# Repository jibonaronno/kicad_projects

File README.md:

# kicad_projects
1. Trailing Edge Dimmer ESP8266

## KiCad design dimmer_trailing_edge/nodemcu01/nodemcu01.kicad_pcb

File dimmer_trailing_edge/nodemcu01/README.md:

# Trailing Edge Dimmer Description

Practically there are 2 types of dimmer. 

1. Raising Edge
2. Trailing Edge

Based on the swithing time position after zero cross detection. 

Here is a simple concept of raising and trailing edge switching.

This project focused on trailing edge dimmer construction. 

Here it stores energy in C5 and C6 from power line ACL and ACN. From the perspective it only uses positive cycle of the phase to store energy. Turning on the mosfet is occured by Opto U2, and turning off is happened by R14 (10k) . So this dimmer is not suitable for more than 200W. 

Found another solution as below:

This 3 channel dimmer is build on ESP8266 NodeMCU . Complete Kicad Drawing is available in [https://github.com/jibonaronno/kicad_projects/tree/main/dimmer_trailing_edge/nodemcu01](https://github.com/jibonaronno/kicad_projects/tree/main/dimmer_trailing_edge/nodemcu01)

The Arduino code is available under qnod01 folder. It is required to provide correct Wifi credentials the the Arduino code and also need to find the IP address of NodeMCU. After successfull connection between Wifi and NodeMCU, user can browse to the NodeMCU IP Address from phone browser and control dimming.

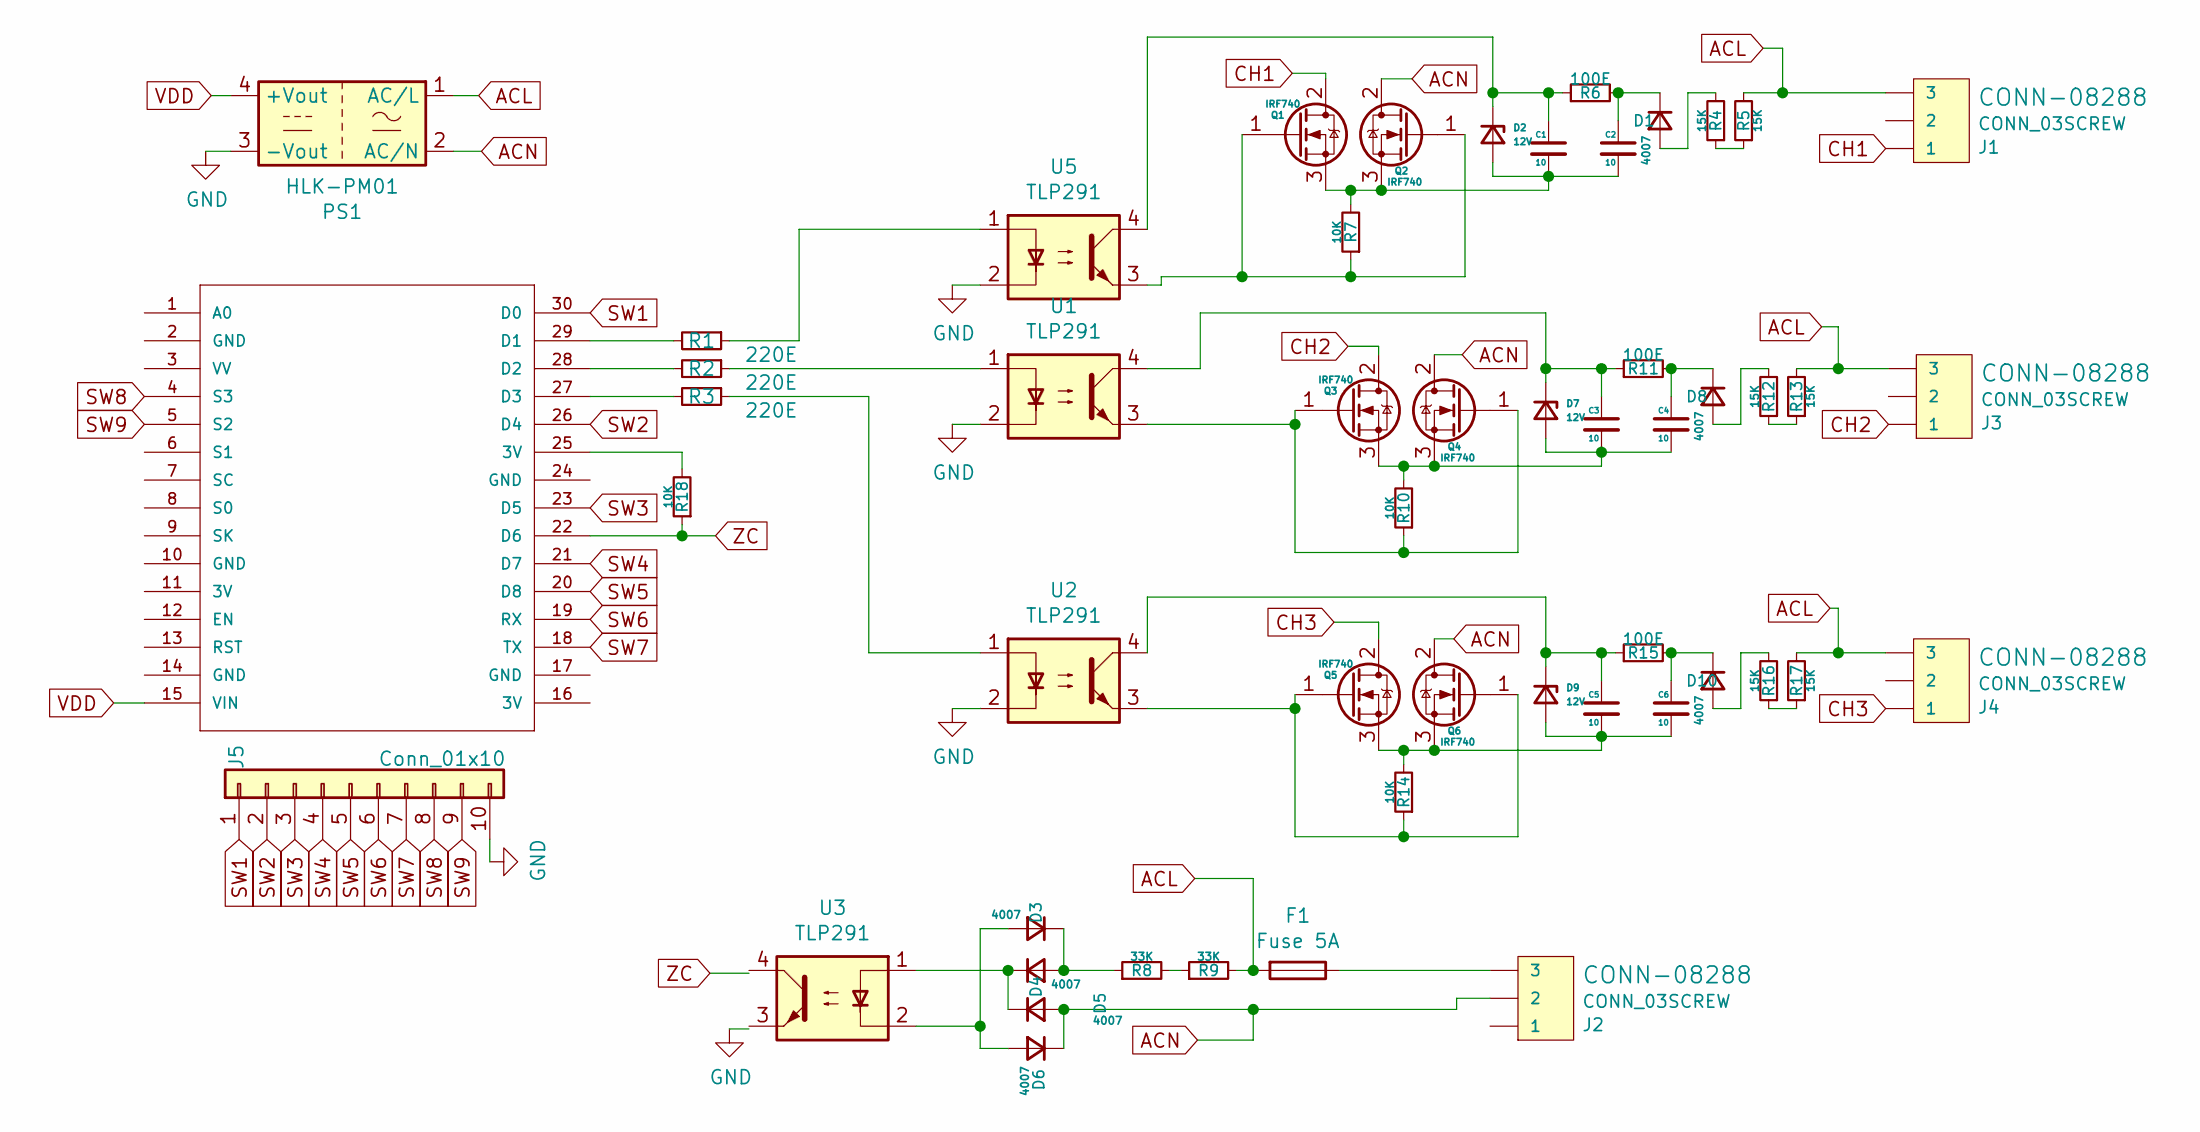
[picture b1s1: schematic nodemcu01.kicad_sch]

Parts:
C1, C2, C3, C4, C5, C6: 10; C_1206_3216Metric
D1, D3, D4, D5, D6, D8, D10: 4007; D_1206_3216Metric
D2, D7, D9: 12V; D_1206_3216Metric
F1: Fuse 5A; Fuseholder5x20_horiz_open_inline_Type-I
J1, J2, J3, J4: CONN_03SCREW; SCREWTERMINAL-3.5MM-3
J5: Conn_01x10; JST_XH_B10B-XH-A_1x10_P2.50mm_Vertical
M1: NODEMCU; nodemcu2-NODEMCU
PS1: HLK-PM01; Converter_ACDC_HiLink_HLK-PMxx
Q1, Q2, Q3, Q4, Q5, Q6: IRF740; TO-220-3_Vertical
R1, R2, R3: 220E; R_0805_2012Metric
R4, R5, R12, R13, R16, R17: 15K; R_1206_3216Metric
R6, R11, R15: 100E; R_1206_3216Metric
R7, R10, R14, R18: 10K; R_1206_3216Metric
R8, R9: 33K; R_1206_3216Metric
U1, U2, U3, U5: TLP291; SOIC-4_4.55x2.6mm_P1.27mm

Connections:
ACL: F1.2, J1.3, J3.3, J4.3, PS1.1 (AC/L), R5.2, R9.2, R13.2, R17.2
ACN: D5.2 (A), D6.1 (K), J2.2, PS1.2 (AC/N), Q2.2 (D), Q4.2 (D), Q6.2 (D)
CH1: J1.1, Q1.2 (D)
CH2: J3.1, Q3.2 (D)
CH3: J4.1, Q5.2 (D)
GND: J5.10, PS1.3 (-Vout), U1.2, U2.2, U3.3, U5.2
unnamed: C1.1, D2.1 (K), R6.1, U5.4
unnamed: C1.2, C2.2, D2.2 (A), Q1.3 (S), Q2.3 (S), R7.2
unnamed: C2.1, D1.1 (K), R6.2
unnamed: C3.1, D7.1 (K), R11.1, U1.4
unnamed: C3.2, C4.2, D7.2 (A), Q3.3 (S), Q4.3 (S), R10.2
unnamed: C4.1, D8.1 (K), R11.2
unnamed: C5.1, D9.1 (K), R15.1, U2.4
unnamed: C5.2, C6.2, D9.2 (A), Q5.3 (S), Q6.3 (S), R14.2
unnamed: C6.1, D10.1 (K), R15.2
unnamed: D1.2 (A), R4.2
unnamed: D3.1 (K), D4.2 (A), R8.1
unnamed: D3.2 (A), D6.2 (A), U3.2
unnamed: D4.1 (K), D5.1 (K), U3.1
unnamed: D8.2 (A), R12.2
unnamed: D10.2 (A), R16.2
unnamed: F1.1, J2.3
unnamed: M1.25 (3V), R18.2
unnamed: M1.27 (D3), R3.2
unnamed: M1.28 (D2), R2.2
unnamed: M1.29 (D1), R1.2
unnamed: Q1.1 (G), Q2.1 (G), R7.1, U5.3
unnamed: Q3.1 (G), Q4.1 (G), R10.1, U1.3
unnamed: Q5.1 (G), Q6.1 (G), R14.1, U2.3
unnamed: R1.1, U5.1
unnamed: R2.1, U1.1
unnamed: R3.1, U2.1
unnamed: R4.1, R5.1
unnamed: R8.2, R9.1
unnamed: R12.1, R13.1
unnamed: R16.1, R17.1
SW1: J5.1, M1.30 (D0)
SW2: J5.2, M1.26 (D4)
SW3: J5.3, M1.23 (D5)
SW4: J5.4, M1.21 (D7)
SW5: J5.5, M1.20 (D8)
SW6: J5.6, M1.19 (RX)
SW7: J5.7, M1.18 (TX)
SW8: J5.8, M1.4 (S3)
SW9: J5.9, M1.5 (S2)
VDD: M1.15 (VIN), PS1.4 (+Vout)
ZC: M1.22 (D6), R18.1, U3.4

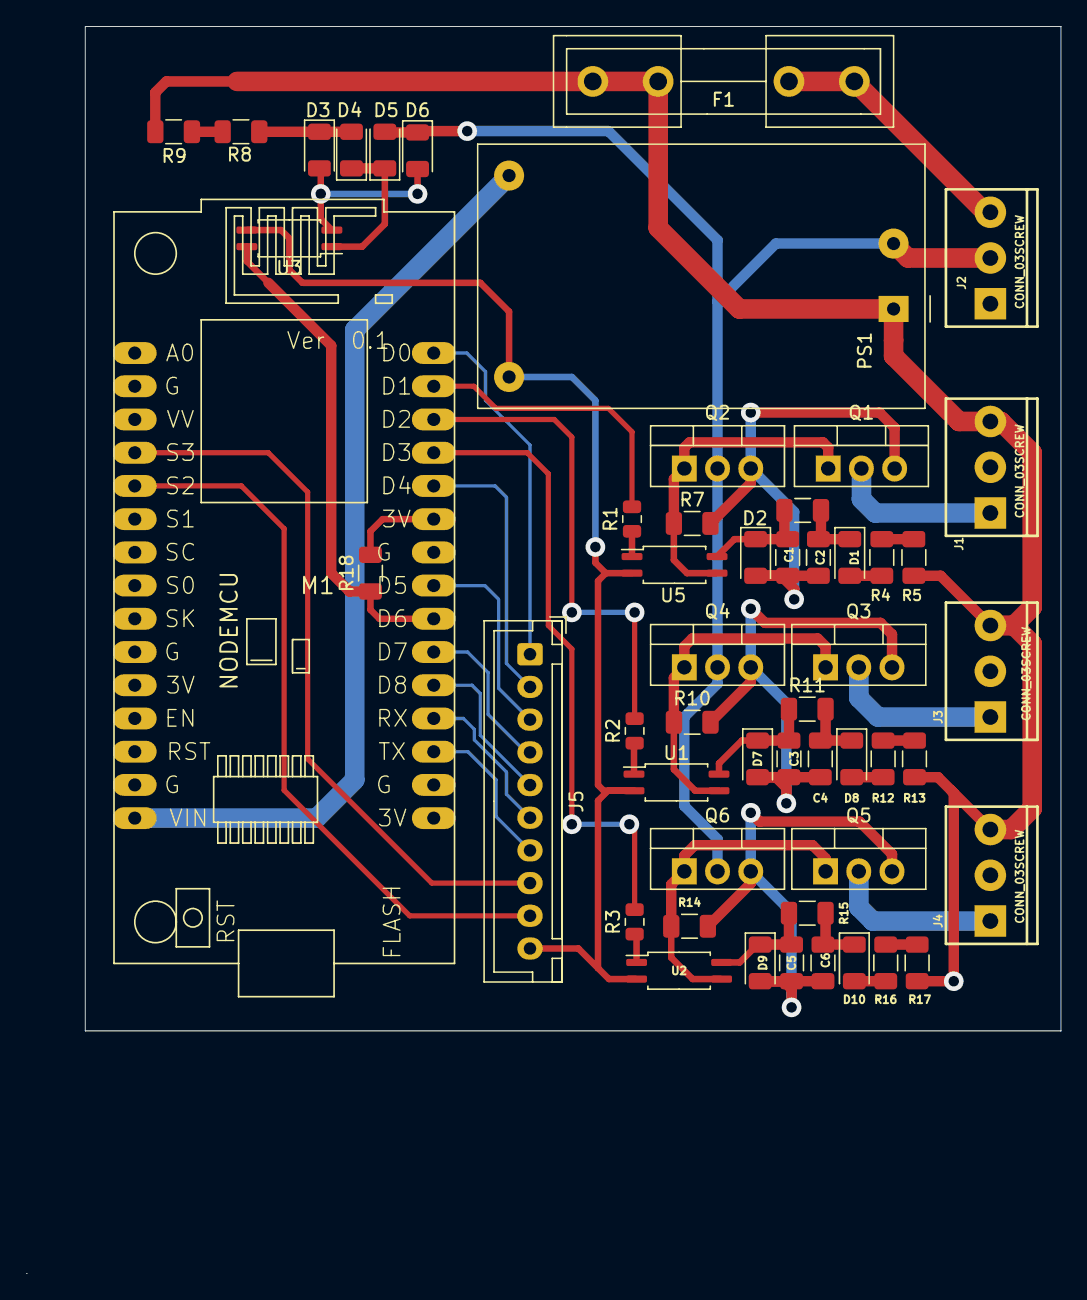
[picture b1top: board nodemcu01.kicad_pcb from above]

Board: 2 copper layers, 79.1 x 95.3 mm, 52 parts (0 on the bottom side), 47 nets.

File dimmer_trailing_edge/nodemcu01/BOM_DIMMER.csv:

"Item","Qty","Reference(s)","Value","LibPart","Footprint","Datasheet","Field4"
"1","6","C1, C2, C3, C4, C5, C6","10uF","Device:C_Small","Capacitor_SMD:C_1206_3216Metric","~",""
"2","7","D1, D3, D4, D5, D6, D8, D10","4007","Device:D_Small","Diode_SMD:D_1206_3216Metric","~",""
"3","3","D2, D7, D9","12V","Device:D_Zener_Small","Diode_SMD:D_1206_3216Metric","~",""
"4","1","F1","Fuse 5A","Device:Fuse","FuseHolder:Fuseholder5x20_horiz_open_inline_Type-I","~",""
"5","4","J1, J2, J3, J4","CONN_03SCREW","SparkFun-Connectors:CONN_03SCREW","Connectors:SCREWTERMINAL-3.5MM-3","","CONN-08288"
"6","1","J5","Conn_01x10","Connector_Generic:Conn_01x10","Connector_JST:JST_XH_B10B-XH-A_1x10_P2.50mm_Vertical","~",""
"7","1","M1","NODEMCU","nodemcu2:NODEMCU ESP8266","nodemcu2:nodemcu2-NODEMCU","",""
"8","1","PS1","HLK-PM01","Converter_ACDC:HLK-PM01","Converter_ACDC:Converter_ACDC_HiLink_HLK-PMxx","http://www.hlktech.net/product_detail.php?ProId=54",""
"9","6","Q1, Q2, Q3, Q4, Q5, Q6","IRF740","Transistor_FET:IRF740","Package_TO_SOT_THT:TO-220-3_Vertical","http://www.vishay.com/docs/91054/91054.pdf",""
"10","3","R1, R2, R3","220E","Device:R_Small","Resistor_SMD:R_0805_2012Metric","~",""
"11","6","R4, R5, R12, R13, R16, R17","15K","Device:R_Small","Resistor_SMD:R_1206_3216Metric","~",""
"12","3","R6, R11, R15","100E","Device:R_Small","Resistor_SMD:R_1206_3216Metric","~",""
"13","4","R7, R10, R14, R18","10K","Device:R_Small","Resistor_SMD:R_1206_3216Metric","~",""
"14","2","R8, R9","33K","Device:R_Small","Resistor_SMD:R_1206_3216Metric","~",""
"15","4","U1, U2, U3, U5","TLP291","Isolator:TLP291","Package_SO:SOIC-4_4.55x2.6mm_P1.27mm","https://toshiba.semicon-storage.com/info/docget.jsp?did=1288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",""

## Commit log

2025-05-19 Dimmer Trailing V1.0
2026-03-30 pdating readme
